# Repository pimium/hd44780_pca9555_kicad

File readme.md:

# HD44780 Driver using PCA555
## Schematic

## Board

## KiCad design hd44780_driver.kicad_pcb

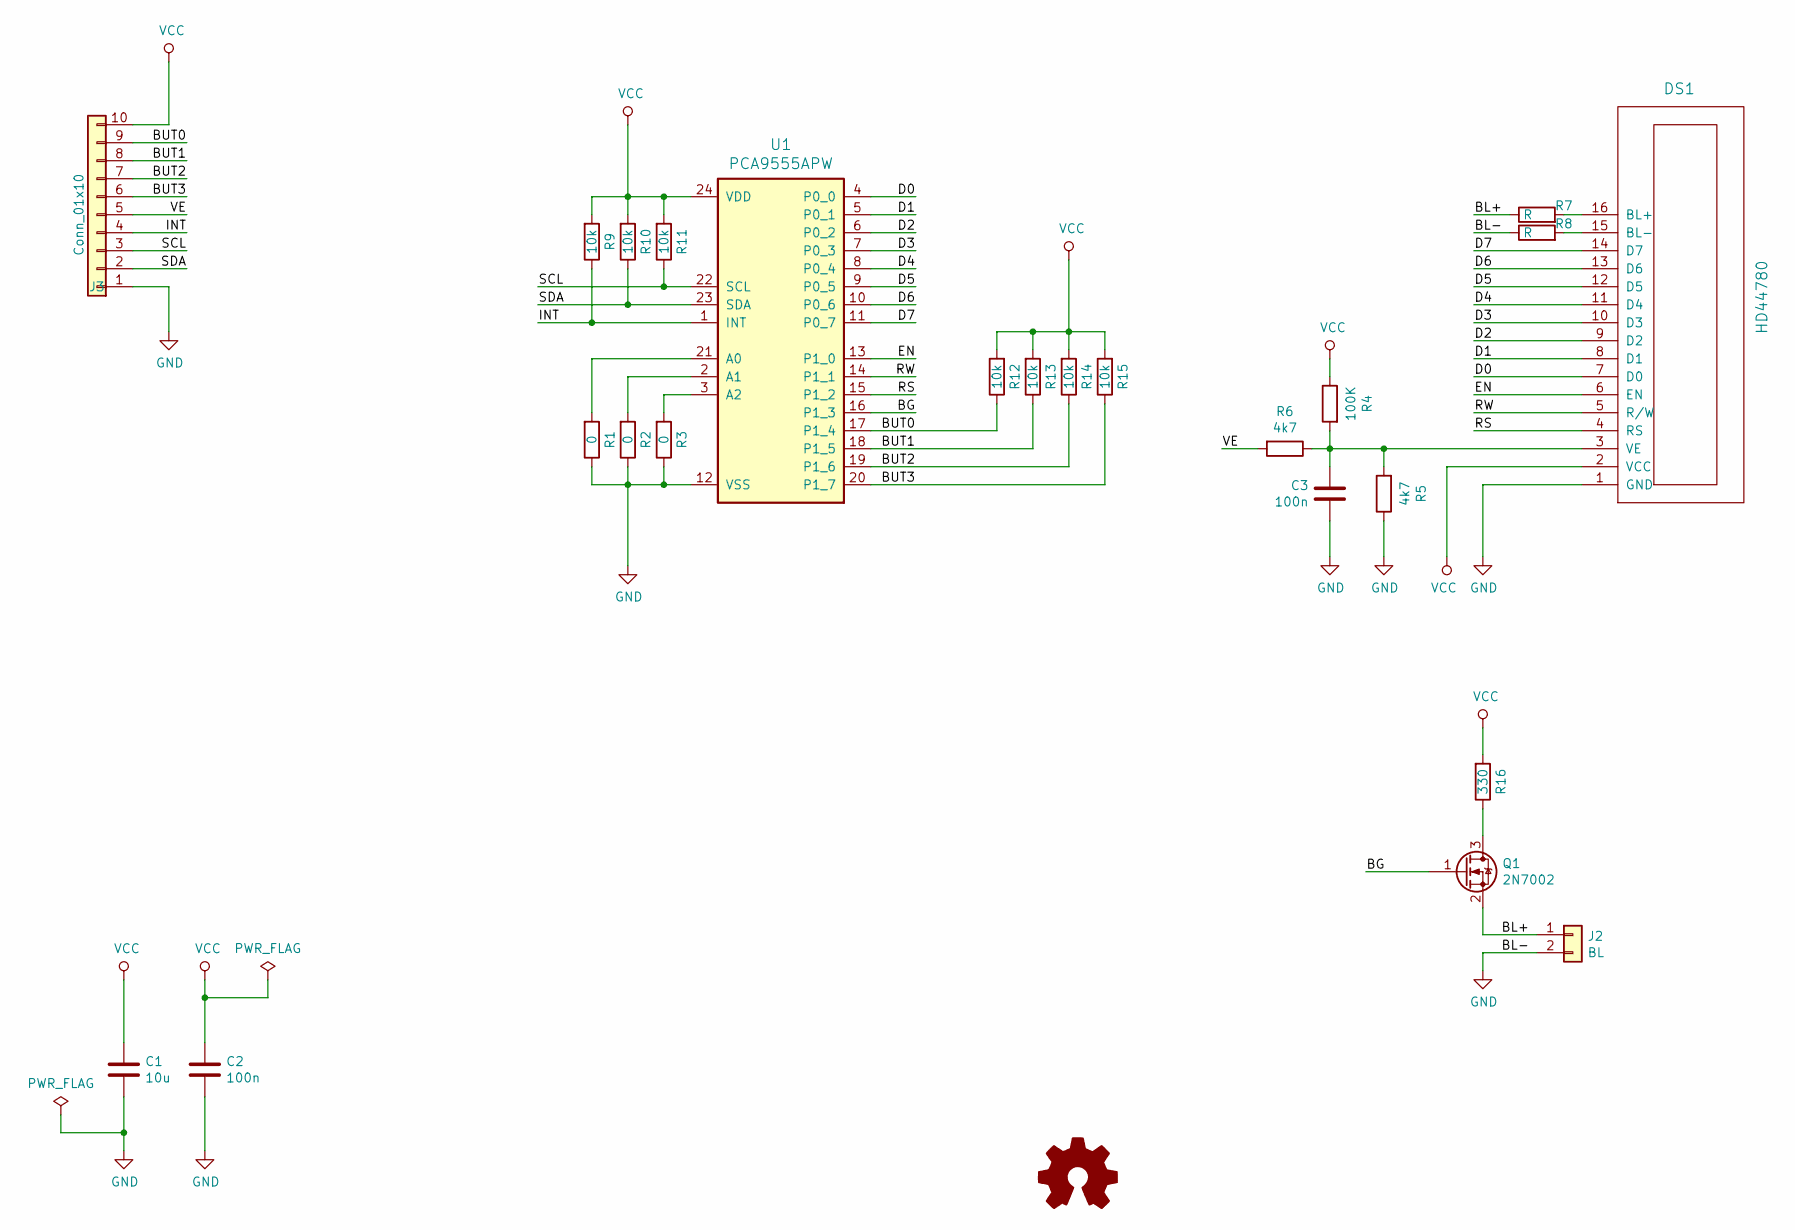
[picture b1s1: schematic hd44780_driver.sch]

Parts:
C1: 10u; C_0805_2012Metric_Pad1.15x1.40mm_HandSolder
C2, C3: 100n; C_0805_2012Metric_Pad1.15x1.40mm_HandSolder
DS1: HD44780; PinHeader_1x16_P2.54mm_Vertical
J2: BL; PinHeader_1x02_P2.54mm_Vertical
J3: Conn_01x10; PinHeader_1x10_P2.54mm_Vertical
Q1: 2N7002; SOT-23
R1, R2, R3: 0; R_0805_2012Metric_Pad1.15x1.40mm_HandSolder
R4: 100K; R_0805_2012Metric_Pad1.15x1.40mm_HandSolder
R5, R6: 4k7; R_0805_2012Metric_Pad1.15x1.40mm_HandSolder
R7, R8: R; R_0805_2012Metric_Pad1.15x1.40mm_HandSolder
R9, R10, R11, R12, R13, R14, R15: 10k; R_0805_2012Metric_Pad1.15x1.40mm_HandSolder
R16: 330; R_0805_2012Metric_Pad1.15x1.40mm_HandSolder
U1: PCA9555APW; SSOP-24_5.3x8.2mm_P0.65mm

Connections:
/BG: Q1.1 (G), U1.16 (P1_3)
/BL+: J2.1, Q1.2 (S), R7.1
/BUT0: J3.9, R12.1, U1.17 (P1_4)
/BUT1: J3.8, R13.1, U1.18 (P1_5)
/BUT2: J3.7, R14.1, U1.19 (P1_6)
/BUT3: J3.6, R15.1, U1.20 (P1_7)
/D0: DS1.7 (D0), U1.4 (P0_0)
/D1: DS1.8 (D1), U1.5 (P0_1)
/D2: DS1.9 (D2), U1.6 (P0_2)
/D3: DS1.10 (D3), U1.7 (P0_3)
/D4: DS1.11 (D4), U1.8 (P0_4)
/D5: DS1.12 (D5), U1.9 (P0_5)
/D6: DS1.13 (D6), U1.10 (P0_6)
/D7: DS1.14 (D7), U1.11 (P0_7)
/EN: DS1.6 (EN), U1.13 (P1_0)
/INT: J3.4, R9.1, U1.1 (INT)
/RS: DS1.4 (RS), U1.15 (P1_2)
/RW: DS1.5 (R/W), U1.14 (P1_1)
/SCL: J3.3, R11.1, U1.22 (SCL)
/SDA: J3.2, R10.1, U1.23 (SDA)
/VE: J3.5, R6.2
GND: C1.2, C2.2, C3.1, DS1.1 (GND), J2.2, J3.1, R1.1, R2.1, R3.1, R5.1, R8.1, U1.12 (VSS)
unnamed: C3.2, DS1.3 (VE), R4.2, R5.2, R6.1
unnamed: DS1.15 (BL-), R8.2
unnamed: DS1.16 (BL+), R7.2
unnamed: Q1.3 (D), R16.1
unnamed: R1.2, U1.21 (A0)
unnamed: R2.2, U1.2 (A1)
unnamed: R3.2, U1.3 (A2)
VCC: C1.1, C2.1, DS1.2 (VCC), J3.10, R4.1, R9.2, R10.2, R11.2, R12.2, R13.2, R14.2, R15.2, R16.2, U1.24 (VDD)

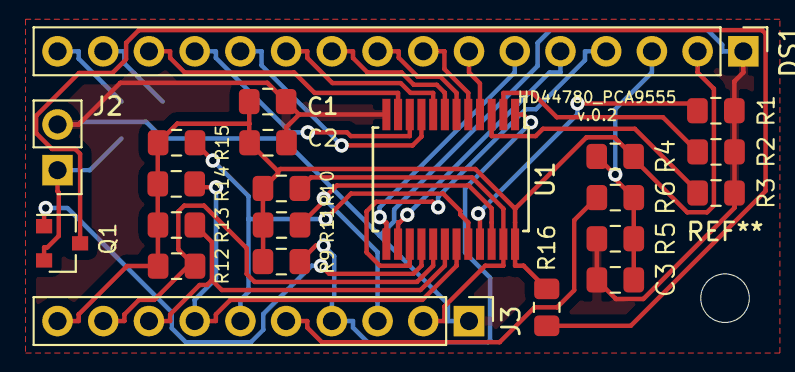
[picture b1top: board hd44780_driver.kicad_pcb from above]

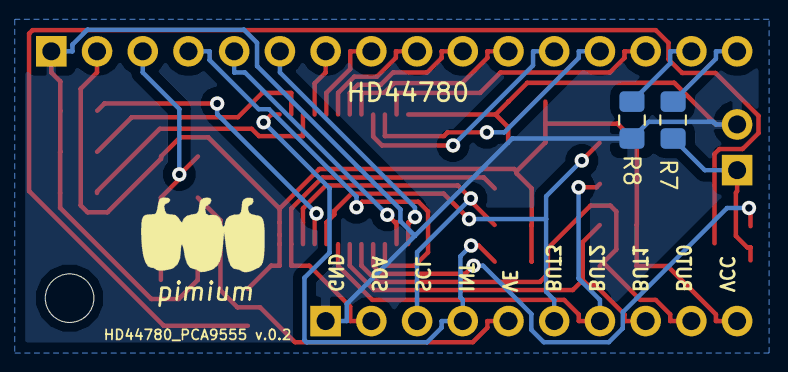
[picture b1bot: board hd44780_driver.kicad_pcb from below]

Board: 2 copper layers, 24 parts (2 on the bottom side), 30 nets.

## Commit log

2021-11-27 add a input and move VE from the expander to the connector
2021-11-27 add readme
2021-11-27 Change the footprint
